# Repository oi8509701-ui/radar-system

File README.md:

X-Band T/R Module (10 GHz) with Fractal Antenna

High-performance single-channel Transmit/Receive (T/R) module for X-band phased array systems (~10–10.5 GHz), featuring integrated beamforming and a compact fractal antenna.
---------------------------------

---------------------------------

High-performance single-channel Transmit/Receive (T/R) module for X-band phased array systems (~10–10.5 GHz), featuring integrated beamforming and a compact fractal antenna.

⸻
 
 Overview

This project implements a single RF front-end module (tile) designed for scalable phased array systems.

Key features:

	•	X-band operation (~10–10.5 GHz)
	•	Integrated PA + LNA + T/R switch (QPM1002)
	•	Beamforming support (phase + amplitude control)
	•	Compact fractal antenna (14×14 mm)
	•	Designed for array scaling (e.g., 256+ elements)
	•	Optimized for automated routing (Freerouting)

⸻
 
 Architecture

RF IN → Phase Shifter → Attenuator → TXIN → [QPM1002] → ANT → Antenna
                                            ▲
RF OUT ← Phase Shifter ← Attenuator ← RXOUT ┘

QPM1002 Internal Structure:

	•	TX path: PA (~35 dBm pulsed)
	•	RX path: LNA (~2.2 dB NF, ~25 dB gain)
	•	Internal T/R switch
	•	Built-in power detector (VDET)

⸻
 
 Power Architecture

Rail	Voltage	Purpose
TX_VD	+25V	Power Amplifier
RX_VD	+10V	LNA
VDD_LOGIC	+5V	Digital logic
VDD_IO	+3.3V	Control interface
VG	-2.5V	GaN gate bias

Converters:

	•	LM5156 (SEPIC) → 25V
	•	LM5017 → 10V / 5V
	•	Charge pump → -2.5V

⸻

RF Components

Component	Function	Notes

QPM1002	T/R front-end	Core RF IC
TGP2109	Phase shifter (6-bit)	8–12 GHz
PE43705	Attenuator (6-bit)	0.5–12 GHz

⸻

 PCB
 
	•	Substrate: Rogers 4350B
	•	Stackup: 4 layers (RF + GND + PWR + CTRL)
	•	Controlled impedance (50 Ω)
	•	Dense via stitching for RF grounding
	•	Optimized for high-frequency layout

⸻

 Thermal Design

Per module dissipation:

Block	Power
PA	~8 W
DC-DC	~5.5 W
Beamforming	~1.3 W
Other	~1 W

Total: ~16 W per module

For 256 modules:

	•	Total ≈ 4 kW
	•	Requires liquid cooling

⸻
 
 Control Interface
 
	•	SPI (phase + attenuation control)
	•	GPIO (TX/RX switching)
	•	I²C (temperature sensors)

Logic:

	•	SN74HC595 (shift register)
	•	SN74LVTH573 (latch)

⸻
 
 Monitoring
 
	•	4× TMP117 temperature sensors:
	•	RF front-end
	•	Power stage
	•	Beamforming chain
	•	PCB ambient

⸻
 
 Power Sequencing

Power-Up:

	1.	Apply VG (-2.5V)
	2.	Disable TX/RX
	3.	Enable RX_VD (10V)
	4.	Enable TX_VD (25V)
	5.	Enable TX/RX

Power-Down:

	1.	Disable TX/RX
	2.	Disable TX_VD
	3.	Disable RX

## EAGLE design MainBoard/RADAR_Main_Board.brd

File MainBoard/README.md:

# Main Board — Основная плата AERIS-10

## Назначение
Основная плата обработки сигналов радара AERIS-10

## Ключевые компоненты
- **FPGA:** Xilinx Artix-7 (XC7A50T/XC7A100T)
- **MCU:** STM32F746ZGT7 (ARM Cortex-M7)
- **ADC:** AD9484 (500 MSPS, 8-bit)
- **DAC:** AD9708 (125 MSPS, 8-bit)
- **Clock:** AD9523-1
- **PLL:** 2× ADF4382ABCCZ (10.5 GHz)
- **Beamforming:** 4× ADAR1000 (16 каналов)
- **Front-end:** 16× ADTR1107
- **Mixer:** 2× LTC5552

## Функции
- Генерация LFM chirp через DAC
- Приём и оцифровка IF сигнала через ADC
- I/Q down-conversion в FPGA
- Beamforming (электронное управление лучом)
- Обработка: FFT, pulse compression, Doppler, CFAR
- USB 3.0 интерфейс (FT601)
- Управление всеми подсистемами через STM32

## Характеристики
| Параметр | Значение |
|----------|----------|
| Частота | 10.5 ГГц |
| Каналов | 16 |
| FPGA | Artix-7 50T/100T |
| ADC | 500 MSPS |
| DAC | 125 MSPS |

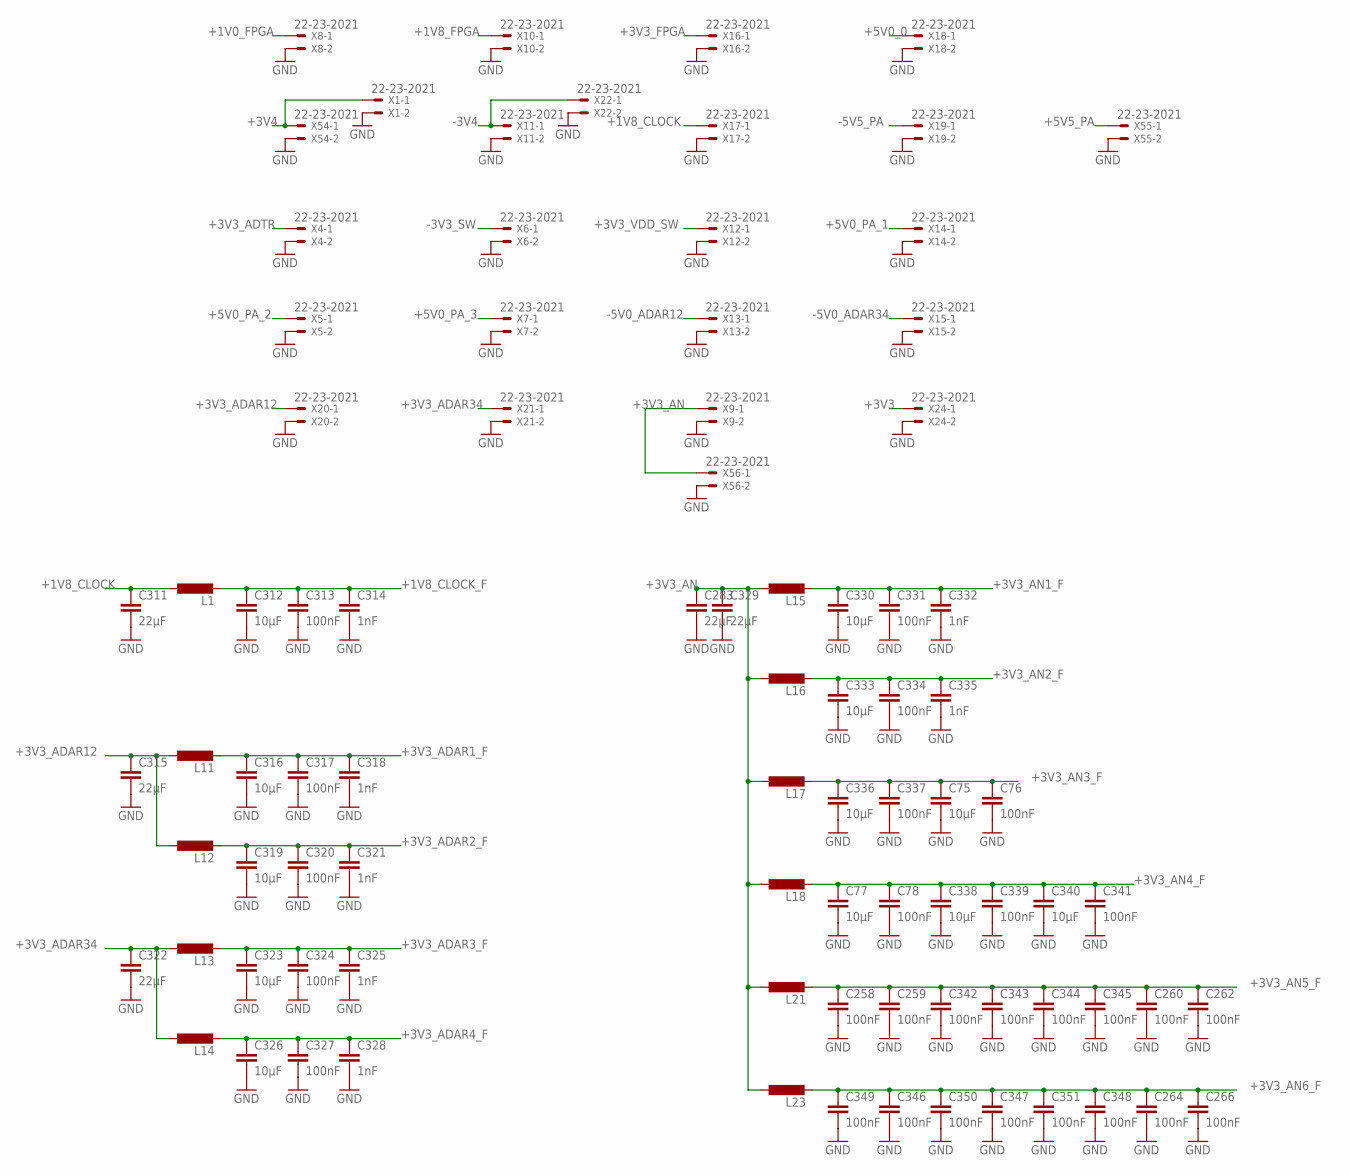
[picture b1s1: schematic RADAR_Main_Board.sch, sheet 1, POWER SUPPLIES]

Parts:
C75, C77, C312, C316, C319, C323, C326, C330, C333, C336, C338, C340: 10µF; C0805
C76, C78, C258, C259, C260, C262, C264, C266, C313, C317, C320, C324, C327, C331, C334, C337, C339, C341, C342, C343, C344, C345, C346, C347, C348, C349, C350, C351: 100nF; C0402
C283, C311, C315, C322, C329: 22µF; C1206
C314, C318, C321, C325, C328, C332, C335: 1nF; C0402
L1, L11, L12, L13, L14, L15, L16, L17, L18, L21, L23: L-EUL5650M; L5650M
X1, X4, X5, X6, X7, X8, X9, X10, X11, X12, X13, X14, X15, X16, X17, X18, X19, X20, X21, X22, X24, X54, X55, X56: 22-23-2021

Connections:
+1V0_FPGA: X8.1; also elsewhere on the board
+1V8_CLOCK: C311.1, L1.1, X17.1
+1V8_CLOCK_F: C312.1, C313.1, C314.1, L1.2; also elsewhere on the board
+1V8_FPGA: X10.1; also elsewhere on the board
+3V3: X24.1; also elsewhere on the board
+3V3_ADAR1_F: C316.1, C317.1, C318.1, L11.2; also elsewhere on the board
+3V3_ADAR2_F: C319.1, C320.1, C321.1, L12.2; also elsewhere on the board
+3V3_ADAR3_F: C323.1, C324.1, C325.1, L13.2; also elsewhere on the board
+3V3_ADAR4_F: C326.1, C327.1, C328.1, L14.2; also elsewhere on the board
+3V3_ADAR12: C315.1, L11.1, L12.1, X20.1
+3V3_ADAR34: C322.1, L13.1, L14.1, X21.1
+3V3_ADTR: X4.1; also elsewhere on the board
+3V3_AN: C283.1, C329.1, L15.1, L16.1, L17.1, L18.1, L21.1, L23.1, X9.1, X56.1; also elsewhere on the board
+3V3_AN1_F: C330.1, C331.1, C332.1, L15.2; also elsewhere on the board
+3V3_AN2_F: C333.1, C334.1, C335.1, L16.2; also elsewhere on the board
+3V3_AN3_F: C75.1, C76.1, C336.1, C337.1, L17.2; also elsewhere on the board
+3V3_AN4_F: C77.1, C78.1, C338.1, C339.1, C340.1, C341.1, L18.2; also elsewhere on the board
+3V3_AN5_F: C258.1, C259.1, C260.1, C262.1, C342.1, C343.1, C344.1, C345.1, L21.2; also elsewhere on the board
+3V3_AN6_F: C264.1, C266.1, C346.1, C347.1, C348.1, C349.1, C350.1, C351.1, L23.2; also elsewhere on the board
+3V3_FPGA: X16.1; also elsewhere on the board
+3V3_VDD_SW: X12.1; also elsewhere on the board
+3V4: X1.1, X54.1; also elsewhere on the board
+5V0_0: X18.1; also elsewhere on the board
+5V0_PA_1: X14.1; also elsewhere on the board
+5V0_PA_2: X5.1; also elsewhere on the board
+5V0_PA_3: X7.1; also elsewhere on the board
+5V5_PA: X55.1; also elsewhere on the board
-3V3_SW: X6.1; also elsewhere on the board
-3V4: X11.1, X22.1; also elsewhere on the board
-5V0_ADAR12: X13.1; also elsewhere on the board
-5V0_ADAR34: X15.1; also elsewhere on the board
-5V5_PA: X19.1; also elsewhere on the board
GND: C75.2, C76.2, C77.2, C78.2, C258.2, C259.2, C260.2, C262.2, C264.2, C266.2, C283.2, C311.2, C312.2, C313.2, C314.2, C315.2, C316.2, C317.2, C318.2, C319.2, C320.2, C321.2, C322.2, C323.2, C324.2, C325.2, C326.2, C327.2, C328.2, C329.2, C330.2, C331.2, C332.2, C333.2, C334.2, C335.2, C336.2, C337.2, C338.2, C339.2, C340.2, C341.2, C342.2, C343.2, C344.2, C345.2, C346.2, C347.2, C348.2, C349.2, C350.2, C351.2, X1.2, X4.2, X5.2, X6.2, X7.2, X8.2, X9.2, X10.2, X11.2, X12.2, X13.2, X14.2, X15.2, X16.2, X17.2, X18.2, X19.2, X20.2, X21.2, X22.2, X24.2, X54.2, X55.2, X56.2; also elsewhere on the board

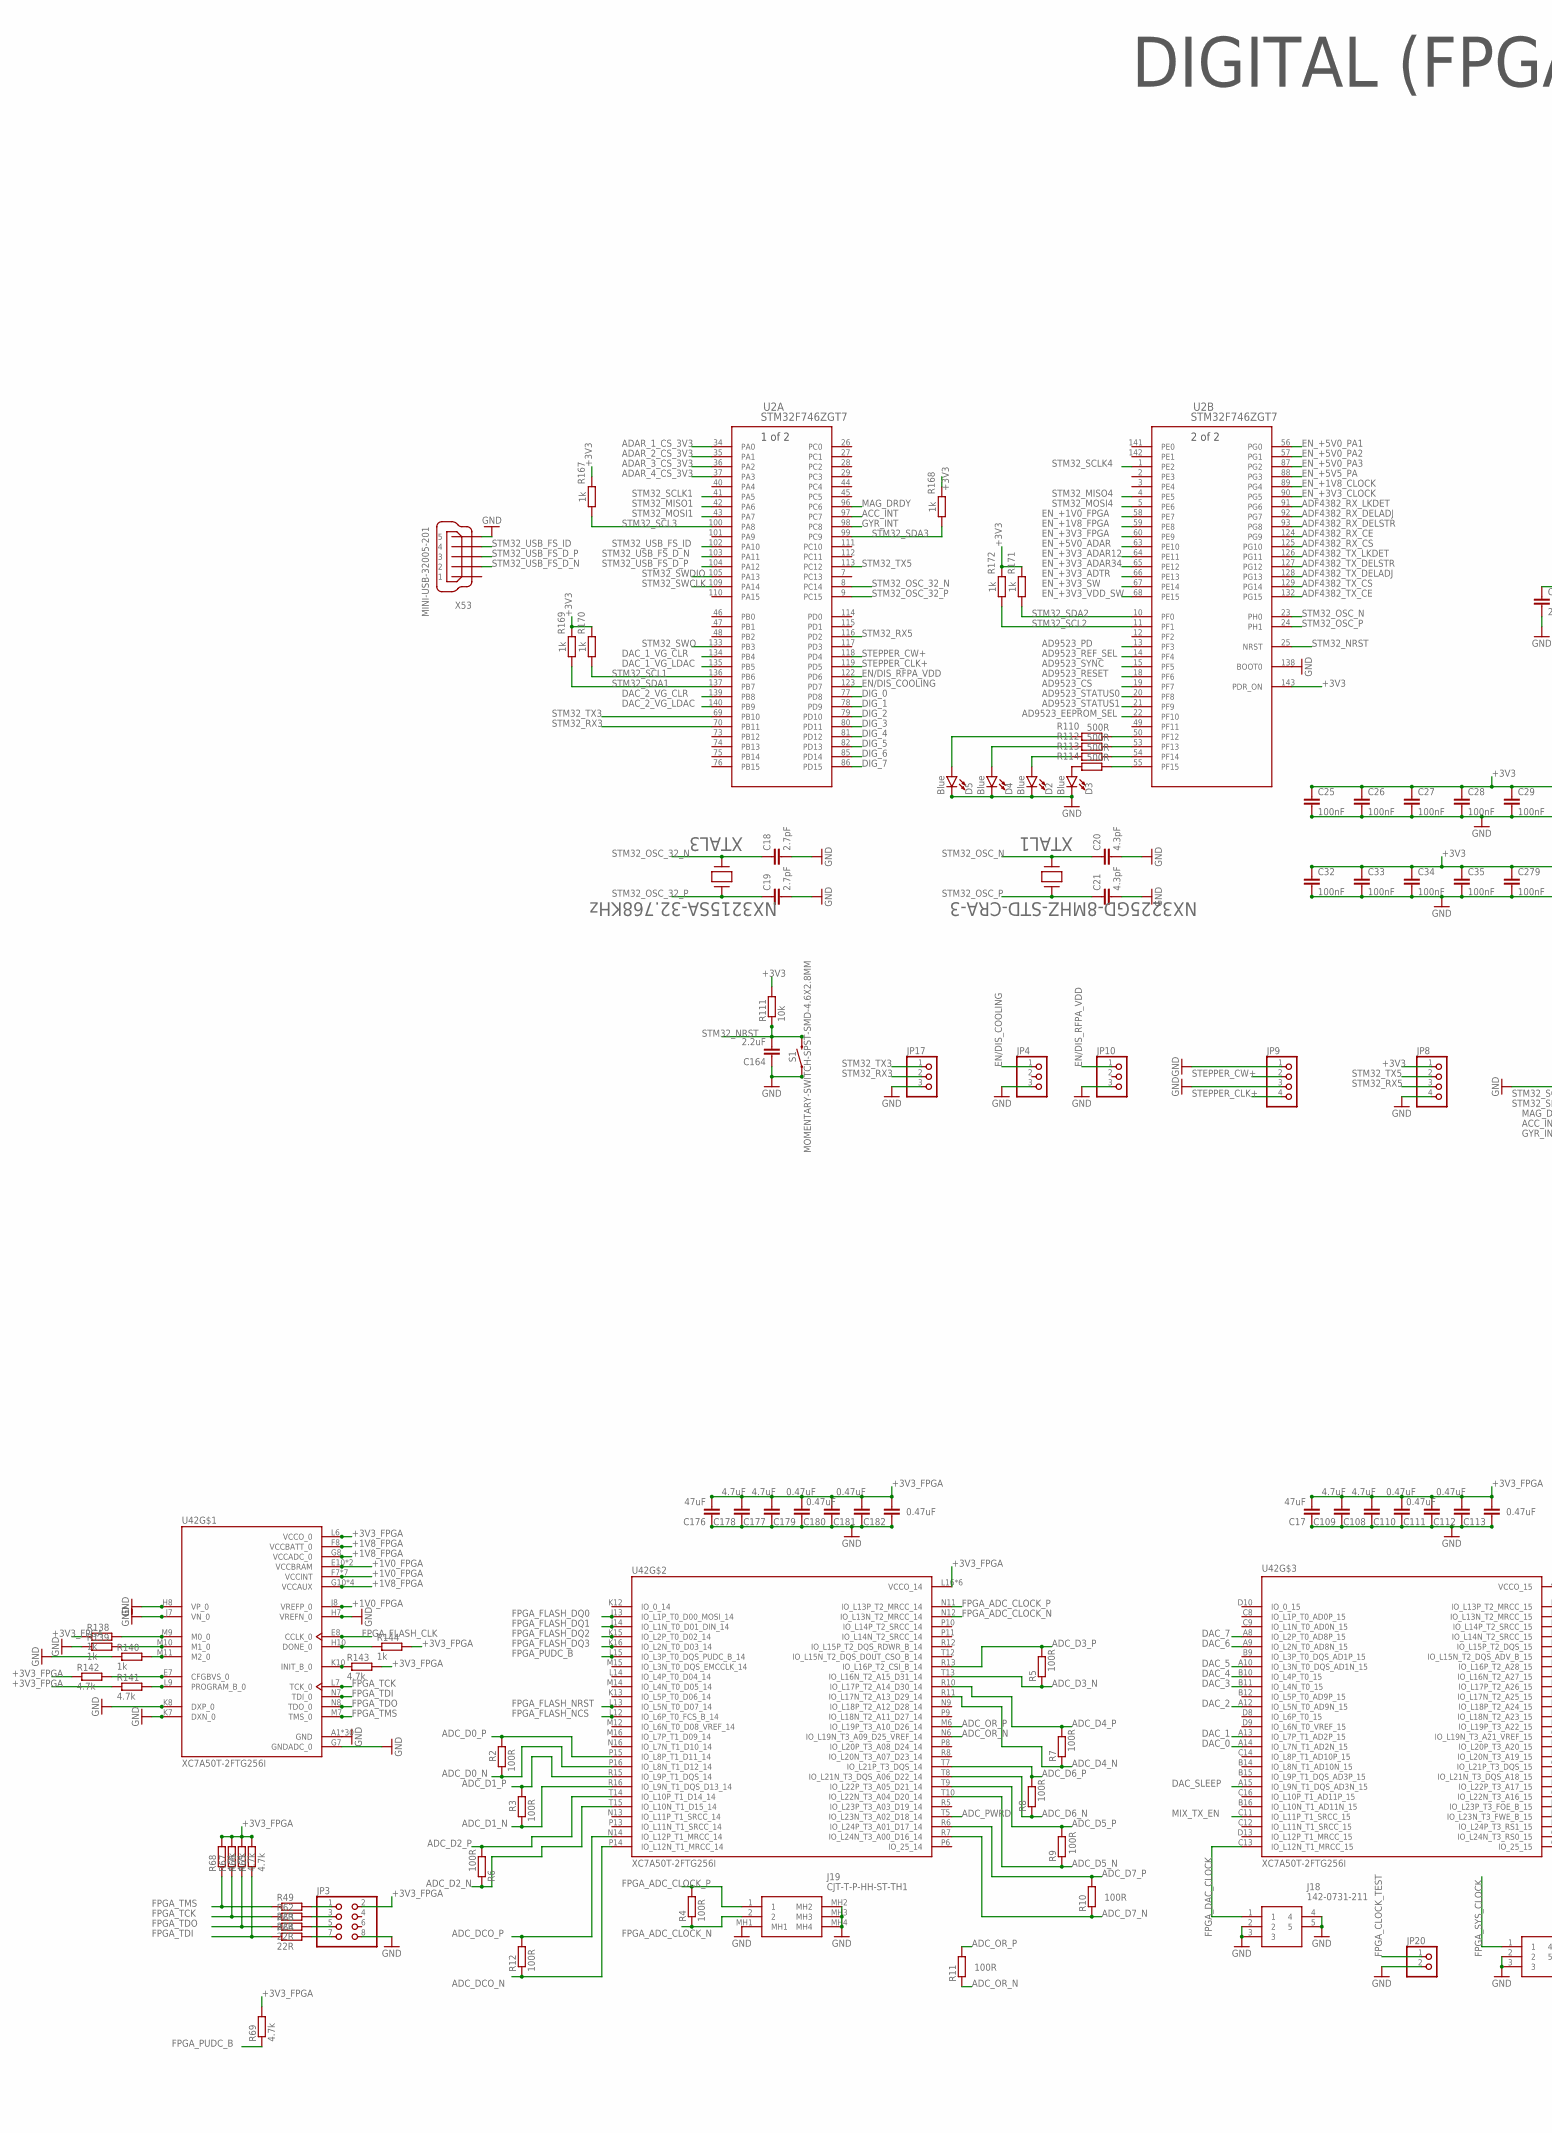
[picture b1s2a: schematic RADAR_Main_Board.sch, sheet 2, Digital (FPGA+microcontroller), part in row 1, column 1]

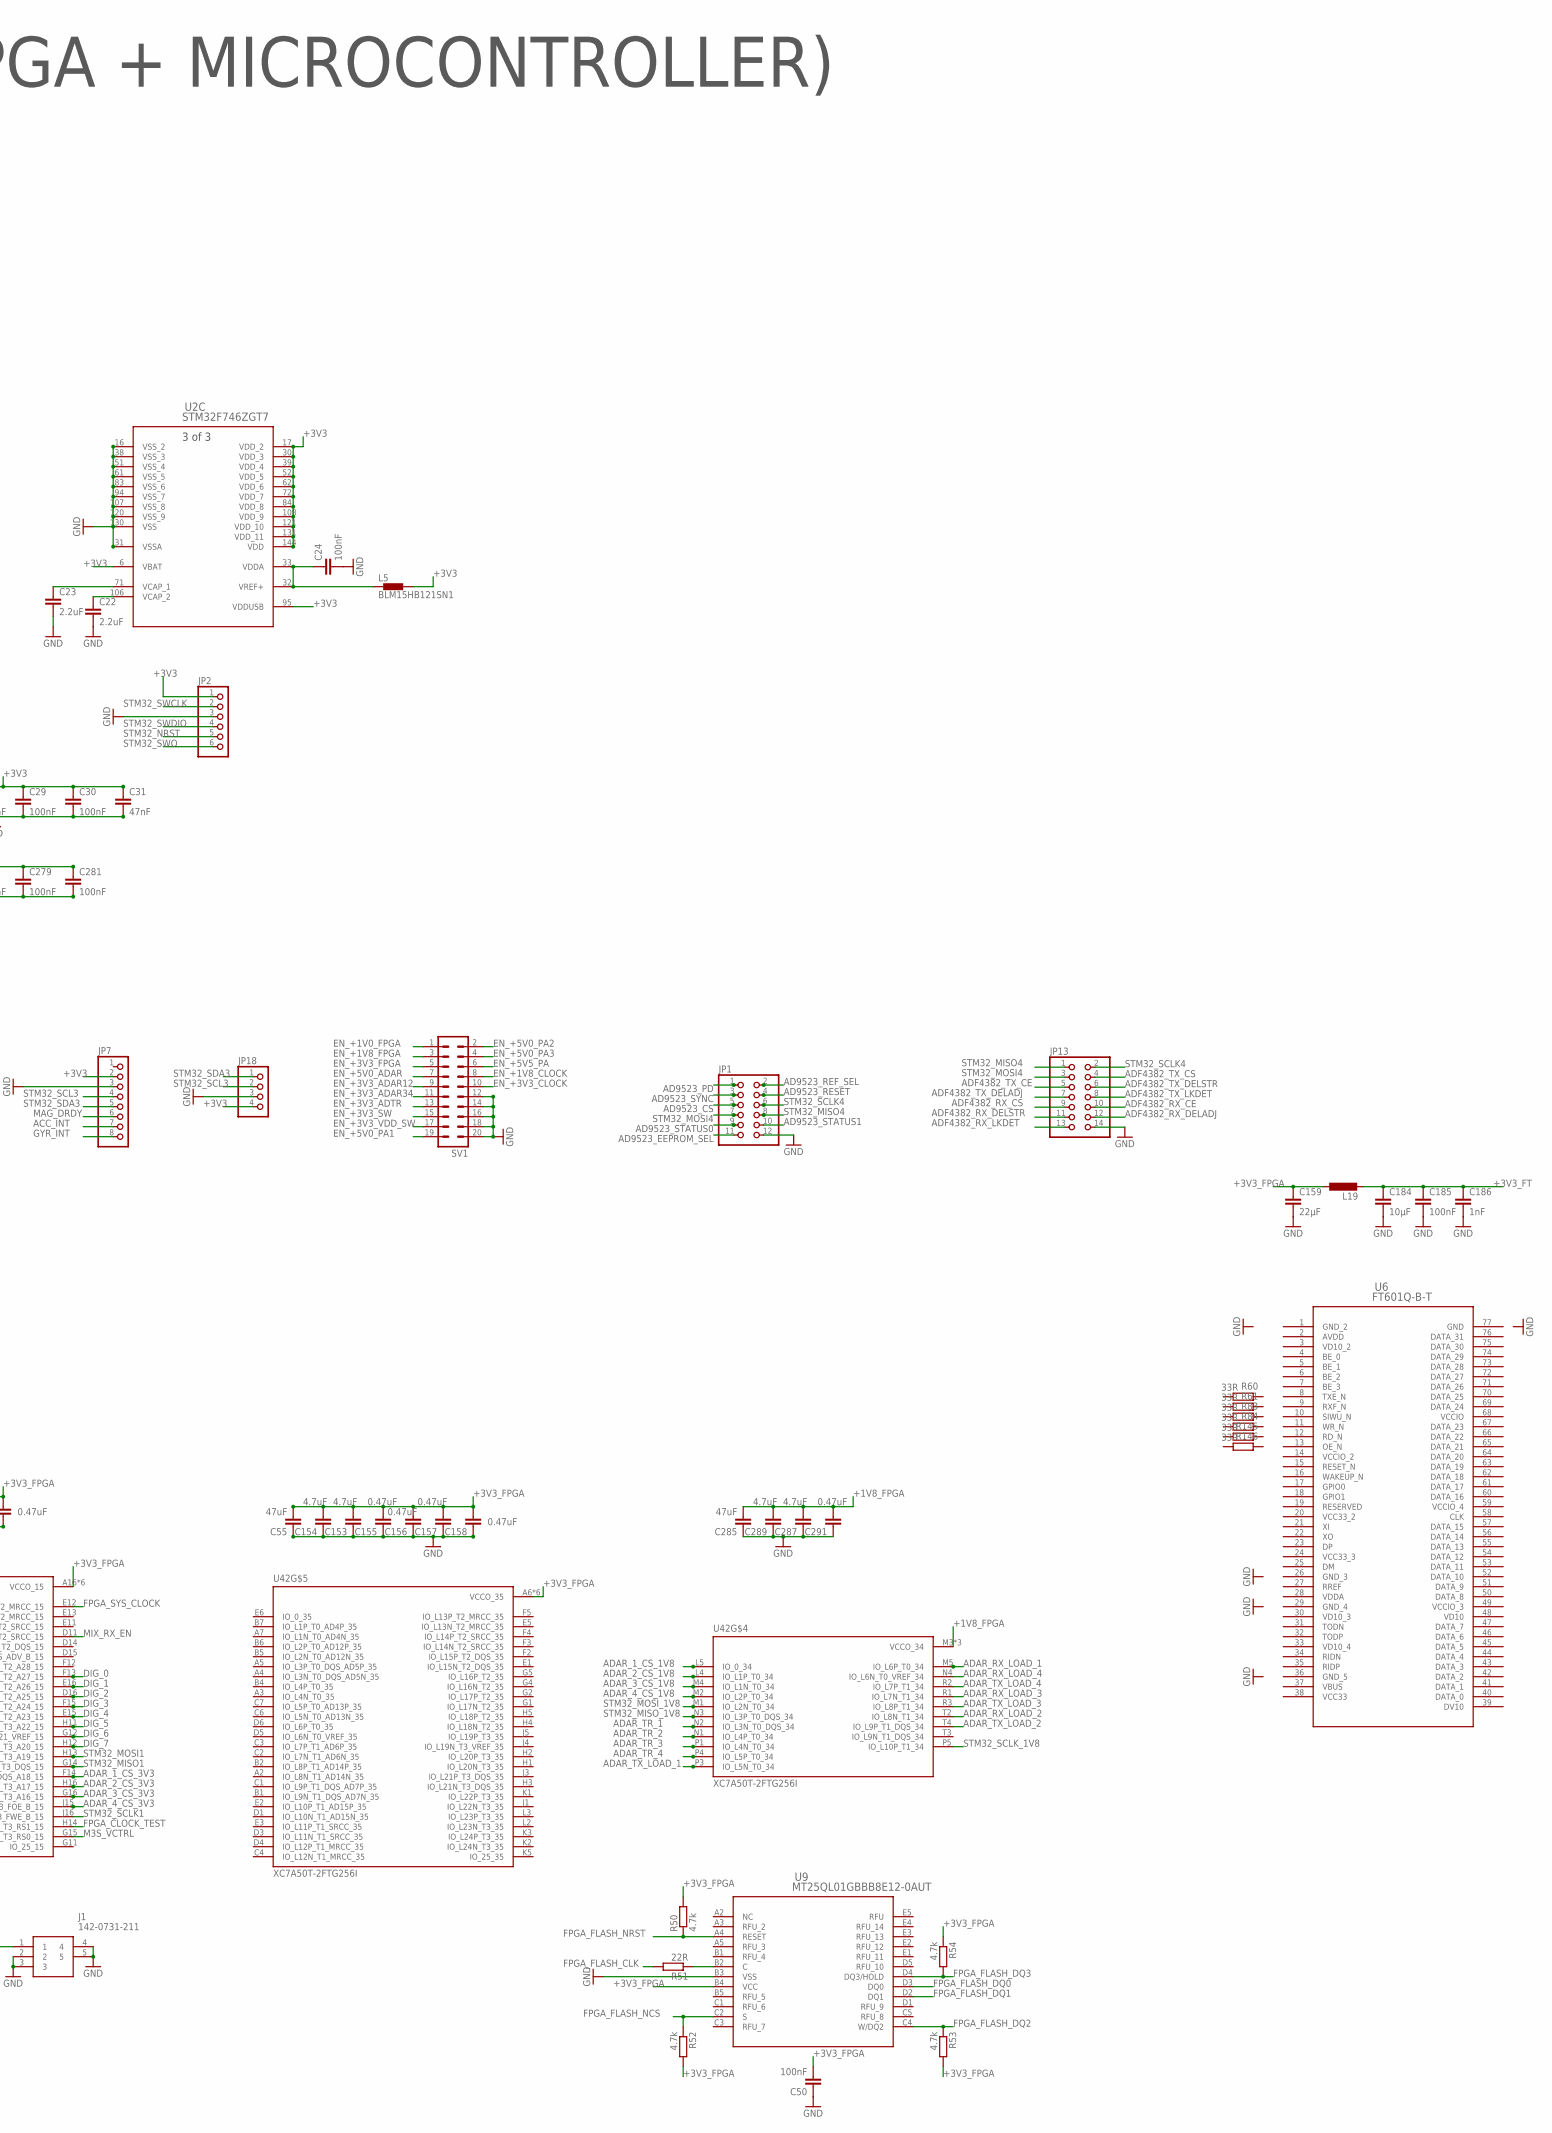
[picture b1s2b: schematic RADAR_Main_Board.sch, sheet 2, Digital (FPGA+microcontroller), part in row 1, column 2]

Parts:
C17, C55, C176, C285: 47uF; C0201
C18, C19: 2.7pF; C0201
C20, C21: 4.3pF; C0201
C22, C23, C164: 2.2uF; C0201
C24, C25, C26, C27, C28, C29, C30, C32, C33, C34, C35, C50, C279, C281: 100nF; C0201
C31: 47nF; C0201
C108, C109, C153, C154, C177, C178, C287, C289: 4.7uF; C0201
C110, C111, C112, C113, C155, C156, C157, C158, C179, C180, C181, C182, C291: 0.47uF; C0201
C159: 22µF; C1206
C184: 10µF; C0805
C185: 100nF; C0402
C186: 1nF; C0402
D2, D3, D4, D5: Blue; LED-0603
J1, J18: 142-0731-211; 1420731211
J19: CJT-T-P-HH-ST-TH1; CJTTPHHSTTH1
JP1: PINHD-2X6; 2X06
JP2: PINHD-1X6; 1X06
JP3: PINHD-2X4; 2X04
JP4, JP10, JP17: PINHD-1X3; 1X03
JP7: PINHD-1X8; 1X08
JP8, JP9, JP18: PINHD-1X4; 1X04
JP13: PINHD-2X7; 2X07
JP20: PINHD-1X2; 1X02
L5: BLM15HB121SN1; 0402
L19: L-EUL5650M; L5650M
R2, R3, R4, R5, R6, R7, R8, R9, R10, R11, R12: 100R; R0201
R49, R51, R62, R63, R64: 22R; R0201
R50, R52, R53, R54, R65, R66, R67, R68, R69, R141, R142, R143: 4.7k; R0201
R60, R61, R83, R84, R145, R146: 33R; R0201
R110, R112, R113, R114: 500R; R0201
R111: 10k; R0201
R138, R139, R140, R144, R167, R168, R169, R170, R171, R172: 1k; R0201
S1: MOMENTARY-SWITCH-SPST-SMD-4.6X2.8MM; TACTILE_SWITCH_SMD_4.6X2.8MM
SV1: MA10-2
U2: STM32F746ZGT7; LQFP-144_STM
U6: FT601Q-B-T; QFN76_FTD
U9: MT25QL01GBBB8E12-0AUT; BGA24_MT25QL_MRN
U42: XC7A50T-2FTG256I; BGA256C100P16X16_1700X1700X155
X53: MINI-USB-32005-201; 32005-201
XTAL1: NX3225GD-8MHZ-STD-CRA-3; XTAL_NX3225GD-8MHZ-STD-CRA-3_N
XTAL3: NX3215SA-32.768KHz; XTAL_NX3225GD-8MHZ-STD-CRA-3_N

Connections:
+1V0_FPGA: U42.E10 (VCCBRAM), U42.F7 (VCCINT), U42.F9 (VCCINT), U42.F11 (VCCBRAM), U42.G6 (VCCINT), U42.H9 (VCCINT), U42.J6 (VCCINT), U42.J8 (VREFP_0), U42.K9 (VCCINT), U42.L8 (VCCINT); also elsewhere on the board
+1V8_FPGA: C285.2, C287.2, C289.2, C291.2, U42.F8 (VCCBATT_0), U42.G8 (VCCADC_0), U42.G10 (VCCAUX), U42.J10 (VCCAUX), U42.K11 (VCCAUX), U42.L10 (VCCAUX), U42.M3 (VCCO_34), U42.R4 (VCCO_34), U42.T1 (VCCO_34); also elsewhere on the board
+3V3: C25.1, C26.1, C27.1, C28.1, C29.1, C30.1, C31.1, C32.1, C33.1, C34.1, C35.1, C279.1, C281.1, JP2.1, JP7.2, JP8.1, JP18.4, L5.2, R111.2, R167.1, R168.1, R169.1, R170.1, R171.1, R172.1, U2.6 (VBAT), U2.17 (VDD_2), U2.30 (VDD_3), U2.39 (VDD_4), U2.52 (VDD_5), U2.62 (VDD_6), U2.72 (VDD_7), U2.84 (VDD_8), U2.95 (VDDUSB), U2.108 (VDD_9), U2.121 (VDD_10), U2.131 (VDD_11), U2.143 (PDR_ON), U2.144 (VDD); also elsewhere on the board
+3V3_FPGA: C17.2, C50.2, C55.2, C108.2, C109.2, C110.2, C111.2, C112.2, C113.2, C153.2, C154.2, C155.2, C156.2, C157.2, C158.2, C159.1, C176.2, C177.2, C178.2, C179.2, C180.2, C181.2, C182.2, JP3.2, L19.1, R50.2, R52.2, R53.2, R54.1, R65.2, R66.2, R67.2, R68.2, R69.2, R138.1, R141.1, R142.1, R143.2, R144.2, U9.B4 (VCC), U42.A6 (VCCO_35), U42.A16 (VCCO_15), U42.B3 (VCCO_35), U42.B13 (VCCO_15), U42.C10 (VCCO_15), U42.D7 (VCCO_35), U42.E4 (VCCO_35), U42.E14 (VCCO_15), U42.F1 (VCCO_35), U42.H15 (VCCO_15), U42.J2 (VCCO_35), U42.J12 (VCCO_15), U42.L6 (VCCO_0), U42.L16 (VCCO_14), U42.M13 (VCCO_14), U42.N10 (VCCO_14), U42.P7 (VCCO_14), U42.R14 (VCCO_14), U42.T11 (VCCO_14); also elsewhere on the board
+3V3_FT: C184.1, C185.1, C186.1, L19.2
ACC_INT: JP7.7, U2.97 (PC7)
AD9523_CS: JP1.5, U2.19 (PF7)
AD9523_EEPROM_SEL: JP1.11, U2.22 (PF10)
AD9523_PD: JP1.1, U2.13 (PF3)
AD9523_REF_SEL: JP1.2, U2.14 (PF4)
AD9523_RESET: JP1.4, U2.18 (PF6)
AD9523_STATUS0: JP1.9, U2.20 (PF8)
AD9523_STATUS1: JP1.10, U2.21 (PF9)
AD9523_SYNC: JP1.3, U2.15 (PF5)
ADAR_1_CS_1V8: U42.L5 (IO_0_34); also elsewhere on the board
ADAR_1_CS_3V3: U2.34 (PA0), U42.F14 (IO_L21N_T3_DQS_A18_15)
ADAR_2_CS_1V8: U42.L4 (IO_L1P_T0_34); also elsewhere on the board
ADAR_2_CS_3V3: U2.35 (PA1), U42.H16 (IO_L22P_T3_A17_15)
ADAR_3_CS_1V8: U42.M4 (IO_L1N_T0_34); also elsewhere on the board
ADAR_3_CS_3V3: U2.36 (PA2), U42.G16 (IO_L22N_T3_A16_15)
ADAR_4_CS_1V8: U42.M2 (IO_L2P_T0_34); also elsewhere on the board
ADAR_4_CS_3V3: U2.37 (PA3), U42.J15 (IO_L23P_T3_FOE_B_15)
ADAR_RX_LOAD_1: U42.M5 (IO_L6P_T0_34); also elsewhere on the board
ADAR_RX_LOAD_2: U42.T2 (IO_L8N_T1_34); also elsewhere on the board
ADAR_RX_LOAD_3: U42.R1 (IO_L7N_T1_34); also elsewhere on the board
ADAR_RX_LOAD_4: U42.N4 (IO_L6N_T0_VREF_34); also elsewhere on the board
ADAR_TR_1: U42.N2 (IO_L3N_T0_DQS_34); also elsewhere on the board
ADAR_TR_2: U42.N1 (IO_L4P_T0_34); also elsewhere on the board
ADAR_TR_3: U42.P1 (IO_L4N_T0_34); also elsewhere on the board
ADAR_TR_4: U42.P4 (IO_L5P_T0_34); also elsewhere on the board
ADAR_TX_LOAD_1: U42.P3 (IO_L5N_T0_34); also elsewhere on the board
ADAR_TX_LOAD_2: U42.T4 (IO_L9P_T1_DQS_34); also elsewhere on the board
ADAR_TX_LOAD_3: U42.R3 (IO_L8P_T1_34); also elsewhere on the board
ADAR_TX_LOAD_4: U42.R2 (IO_L7P_T1_34); also elsewhere on the board
ADC_D0_N: R2.1, U42.P16 (IO_L8N_T1_D12_14); also elsewhere on the board
ADC_D0_P: R2.2, U42.P15 (IO_L8P_T1_D11_14); also elsewhere on the board
ADC_D1_N: R3.1, U42.R16 (IO_L9N_T1_DQS_D13_14); also elsewhere on the board
ADC_D1_P: R3.2, U42.R15 (IO_L9P_T1_DQS_14); also elsewhere on the board
ADC_D2_N: R6.1, U42.T15 (IO_L10N_T1_D15_14); also elsewhere on the board
ADC_D2_P: R6.2, U42.T14 (IO_L10P_T1_D14_14); also elsewhere on the board
ADC_D3_N: R5.1, U42.T13 (IO_L16N_T2_A15_D31_14); also elsewhere on the board
ADC_D3_P: R5.2, U42.R13 (IO_L16P_T2_CSI_B_14); also elsewhere on the board
ADC_D4_N: R7.1, U42.R11 (IO_L17N_T2_A13_D29_14); also elsewhere on the board
ADC_D4_P: R7.2, U42.R10 (IO_L17P_T2_A14_D30_14); also elsewhere on the board
ADC_D5_N: R9.1, U42.T10 (IO_L22N_T3_A04_D20_14); also elsewhere on the board
ADC_D5_P: R9.2, U42.T9 (IO_L22P_T3_A05_D21_14); also elsewhere on the board
ADC_D6_N: R8.1, U42.T8 (IO_L21N_T3_DQS_A06_D22_14); also elsewhere on the board
ADC_D6_P: R8.2, U42.T7 (IO_L21P_T3_DQS_14); also elsewhere on the board
ADC_D7_N: R10.1, U42.R7 (IO_L24N_T3_A00_D16_14); also elsewhere on the board
ADC_D7_P: R10.2, U42.R6 (IO_L24P_T3_A01_D17_14); also elsewhere on the board
ADC_DCO_N: R12.1, U42.P14 (IO_L12N_T1_MRCC_14); also elsewhere on the board
ADC_DCO_P: R12.2, U42.N14 (IO_L12P_T1_MRCC_14); also elsewhere on the board
ADC_OR_N: R11.1, U42.N6 (IO_L19N_T3_A09_D25_VREF_14); also elsewhere on the board
ADC_OR_P: R11.2, U42.M6 (IO_L19P_T3_A10_D26_14); also elsewhere on the board
ADC_PWRD: U42.T5 (IO_L23N_T3_A02_D18_14); also elsewhere on the board
ADF4382_RX_CE: JP13.10, U2.124 (PG9)
ADF4382_RX_CS: JP13.9, U2.125 (PG10)
ADF4382_RX_DELADJ: JP13.12, U2.92 (PG7)
ADF4382_RX_DELSTR: JP13.11, U2.93 (PG8)
ADF4382_RX_LKDET: JP13.13, U2.91 (PG6)
ADF4382_TX_CE: JP13.5, U2.132 (PG15)
ADF4382_TX_CS: JP13.4, U2.129 (PG14)
ADF4382_TX_DELADJ: JP13.7, U2.128 (PG13)
ADF4382_TX_DELSTR: JP13.6, U2.127 (PG12)
ADF4382_TX_LKDET: JP13.8, U2.126 (PG11)
AVDD: U6.2 (AVDD)
DAC_0: U42.A14 (IO_L7N_T1_AD2N_15); also elsewhere on the board
DAC_1: U42.A13 (IO_L7P_T1_AD2P_15); also elsewhere on the board
DAC_1_VG_CLR: U2.134 (PB4); also elsewhere on the board
DAC_1_VG_LDAC: U2.135 (PB5); also elsewhere on the board
DAC_2: U42.A12 (IO_L5N_T0_AD9N_15); also elsewhere on the board
DAC_2_VG_CLR: U2.139 (PB8); also elsewhere on the board
DAC_2_VG_LDAC: U2.140 (PB9); also elsewhere on the board
DAC_3: U42.B11 (IO_L4N_T0_15); also elsewhere on the board
DAC_4: U42.B10 (IO_L4P_T0_15); also elsewhere on the board
DAC_5: U42.A10 (IO_L3N_T0_DQS_AD1N_15); also elsewhere on the board
DAC_6: U42.A9 (IO_L2N_T0_AD8N_15); also elsewhere on the board
DAC_7: U42.A8 (IO_L2P_T0_AD8P_15); also elsewhere on the board
DAC_SLEEP: U42.A15 (IO_L9N_T1_DQS_AD3N_15); also elsewhere on the board
DIG_0: U2.77 (PD8), U42.F13 (IO_L16N_T2_A27_15)
DIG_1: U2.78 (PD9), U42.E16 (IO_L17P_T2_A26_15)
DIG_2: U2.79 (PD10), U42.D16 (IO_L17N_T2_A25_15)
DIG_3: U2.80 (PD11), U42.F15 (IO_L18P_T2_A24_15)
DIG_4: U2.81 (PD12), U42.E15 (IO_L18N_T2_A23_15)
DIG_5: U2.82 (PD13), U42.H11 (IO_L19P_T3_A22_15)
DIG_6: U2.85 (PD14), U42.G12 (IO_L19N_T3_A21_VREF_15)
DIG_7: U2.86 (PD15), U42.H12 (IO_L20P_T3_A20_15)
EN/DIS_COOLING: JP4.1, U2.123 (PD7)
EN/DIS_RFPA_VDD: JP10.1, U2.122 (PD6)
EN_+1V0_FPGA: SV1.1, U2.58 (PE7)
EN_+1V8_CLOCK: SV1.8, U2.89 (PG4)
EN_+1V8_FPGA: SV1.3, U2.59 (PE8)
EN_+3V3_ADAR12: SV1.9, U2.64 (PE11)
EN_+3V3_ADAR34: SV1.11, U2.65 (PE12)
EN_+3V3_ADTR: SV1.13, U2.66 (PE13)
EN_+3V3_CLOCK: SV1.10, U2.90 (PG5)
EN_+3V3_FPGA: SV1.5, U2.60 (PE9)
EN_+3V3_SW: SV1.15, U2.67 (PE14)
EN_+3V3_VDD_SW: SV1.17, U2.68 (PE15)
EN_+5V0_ADAR: SV1.7, U2.63 (PE10)
EN_+5V0_PA1: SV1.19, U2.56 (PG0)
EN_+5V0_PA2: SV1.2, U2.57 (PG1)
EN_+5V0_PA3: SV1.4, U2.87 (PG2)
EN_+5V5_PA: SV1.6, U2.88 (PG3)
FPGA_ADC_CLOCK_N: J19.2, R4.1, U42.N12 (IO_L13N_T2_MRCC_14)
FPGA_ADC_CLOCK_P: J19.1, R4.2, U42.N11 (IO_L13P_T2_MRCC_14)
FPGA_CLOCK_TEST: JP20.1, U42.H14 (IO_L24P_T3_RS1_15)
FPGA_DAC_CLOCK: J18.1, U42.C13 (IO_L12N_T1_MRCC_15)
FPGA_FLASH_CLK: R51.2, U42.E8 (CCLK_0)
FPGA_FLASH_DQ0: U9.D3 (DQ0), U42.J13 (IO_L1P_T0_D00_MOSI_14)
FPGA_FLASH_DQ1: U9.D2 (DQ1), U42.J14 (IO_L1N_T0_D01_DIN_14)
FPGA_FLASH_DQ2: R53.1, U9.C4 (W/DQ2), U42.K15 (IO_L2P_T0_D02_14)
FPGA_FLASH_DQ3: R54.2, U9.D4 (DQ3/HOLD), U42.K16 (IO_L2N_T0_D03_14)
FPGA_FLASH_NCS: R52.1, U9.C2 (S), U42.L12 (IO_L6P_T0_FCS_B_14)
FPGA_FLASH_NRST: R50.1, U9.A4 (RESET), U42.L13 (IO_L5N_T0_D07_14)
FPGA_PUDC_B: R69.1, U42.L15 (IO_L3P_T0_DQS_PUDC_B_14)
FPGA_SYS_CLOCK: J1.1, U42.E12 (IO_L13P_T2_MRCC_15)
FPGA_TCK: R62.1, R67.1, U42.L7 (TCK_0)
FPGA_TDI: R64.1, R65.1, U42.N7 (TDI_0)
FPGA_TDO: R63.1, R66.1, U42.N8 (TDO_0)
FPGA_TMS: R49.1, R68.1, U42.M7 (TMS_0)
GND: C17.1, C18.2, C19.2, C20.2, C21.2, C22.2, C23.2, C24.2, C25.2, C26.2, C27.2, C28.2, C29.2, C30.2, C31.2, C32.2, C33.2, C34.2, C35.2, C50.1, C55.1, C108.1, C109.1, C110.1, C111.1, C112.1, C113.1, C153.1, C154.1, C155.1, C156.1, C157.1, C158.1, C159.2, C164.1, C176.1, C177.1, C178.1, C179.1, C180.1, C181.1, C182.1, C184.2, C185.2, C186.2, C279.2, C281.2, C285.1, C287.1, C289.1, C291.1, D2.C, D3.C, D4.C, D5.C, J1.2, J1.3, J1.4, J1.5, J18.2, J18.3, J18.4, J18.5, J19.MH1, J19.MH2, J19.MH3, J19.MH4, JP1.12, JP2.3, JP3.8, JP4.3, JP7.3, JP8.4, JP9.1, JP9.3, JP10.3, JP13.14, JP17.3, JP18.3, JP20.2, R139.1, R140.1, S1.1, S1.2 (1), SV1.12, SV1.14, SV1.16, SV1.18, SV1.20, U2.16 (VSS_2), U2.31 (VSSA), U2.38 (VSS_3), U2.51 (VSS_4), U2.61 (VSS_5), U2.83 (VSS_6), U2.94 (VSS_7), U2.107 (VSS_8), U2.120 (VSS_9), U2.130 (VSS), U2.138 (BOOT0), U9.B3 (VSS), U42.A1 (GND), U42.A11 (GND), U42.B8 (GND), U42.C5 (GND), U42.C15 (GND), U42.D2 (GND), U42.D12 (GND), U42.E9 (GND), U42.F6 (GND), U42.F10 (GND), U42.F16 (GND), U42.G3 (GND), U42.G7 (GNDADC_0), U42.G9 (GND), U42.G13 (GND), U42.H6 (GND), U42.H7 (VREFN_0), U42.H8 (VP_0), U42.J7 (VN_0), U42.J9 (GND), U42.J11 (GND), U42.K4 (GND), U42.K6 (GND), U42.K7 (DXN_0), U42.K8 (DXP_0), U42.K14 (GND), U42.L1 (GND), U42.L11 (GND), U42.M8 (GND), U42.N5 (GND), U42.N15 (GND), U42.P2 (GND), U42.P12 (GND), U42.R9 (GND), U42.T6 (GND), U42.T16 (GND), X53.5; also elsewhere on the board
GYR_INT: JP7.8, U2.98 (PC8)
M3S_VCTRL: U42.G15 (IO_L24N_T3_RS0_15); also elsewhere on the board
MAG_DRDY: JP7.6, U2.96 (PC6)
MIX_RX_EN: U42.D11 (IO_L14N_T2_SRCC_15); also elsewhere on the board
MIX_TX_EN: U42.C11 (IO_L11P_T1_SRCC_15); also elsewhere on the board
unnamed: C23.1, U2.71 (VCAP_1)
unnamed: C22.1, U2.106 (VCAP_2)
unnamed: C24.1, L5.1, U2.32 (VREF+), U2.33 (VDDA)
unnamed: R51.1, U9.B2 (C)
unnamed: JP3.1, R49.2
unnamed: JP3.3, R62.2
unnamed: JP3.5, R63.2
unnamed: JP3.7, R64.2
unnamed: R110.2, U2.50 (PF12)
unnamed: R112.2, U2.53 (PF13)
unnamed: D3.A, R114.1
unnamed: R113.2, U2.54 (PF14)
unnamed: R114.2, U2.55 (PF15)
unnamed: D2.A, R113.1
unnamed: D4.A, R112.1
unnamed: D5.A, R110.1
unnamed: R138.2, U42.M9 (M0_0)
unnamed: R139.2, U42.M10 (M1_0)
unnamed: R140.2, U42.M11 (M2_0)
unnamed: R141.2, U42.L9 (PROGRAM_B_0)
unnamed: R142.2, U42.E7 (CFGBVS_0)
unnamed: R144.1, U42.H10 (DONE_0)
unnamed: R143.1, U42.K10 (INIT_B_0)
STEPPER_CLK+: JP9.4, U2.119 (PD5)
STEPPER_CW+: JP9.2, U2.118 (PD4)
STM32_MISO1: U2.42 (PA6), U42.G14 (IO_L21P_T3_DQS_15)
STM32_MISO4: JP1.8, JP13.1, U2.4 (PE5)
STM32_MISO_1V8: U42.N3 (IO_L3P_T0_DQS_34); also elsewhere on the board
STM32_MOSI1: U2.43 (PA7), U42.H13 (IO_L20N_T3_A19_15)
STM32_MOSI4: JP1.7, JP13.3, U2.5 (PE6)
STM32_MOSI_1V8: U42.M1 (IO_L2N_T0_34); also elsewhere on the board
STM32_NRST: C164.2, JP2.5, R111.1, S1.3 (2), S1.4 (2), U2.25 (NRST)
STM32_OSC_32_N: C18.1, U2.8 (PC14), XTAL3.2
STM32_OSC_32_P: C19.1, U2.9 (PC15), XTAL3.1
STM32_OSC_N: C20.1, U2.23 (PH0), XTAL1.2
STM32_OSC_P: C21.1, U2.24 (PH1), XTAL1.1
STM32_RX3: JP17.2, U2.70 (PB11)
STM32_RX5: JP8.3, U2.116 (PD2)
STM32_SCL1: R170.2, U2.136 (PB6); also elsewhere on the board
STM32_SCL2: R172.2, U2.11 (PF1); also elsewhere on the board
STM32_SCL3: JP7.4, JP18.2, R167.2, U2.100 (PA8)
STM32_SCLK1: U2.41 (PA5), U42.J16 (IO_L23N_T3_FWE_B_15)
STM32_SCLK4: JP1.6, JP13.2, U2.1 (PE2)
STM32_SCLK_1V8: U42.P5 (IO_L10P_T1_34); also elsewhere on the board
STM32_SDA1: R169.2, U2.137 (PB7); also elsewhere on the board
STM32_SDA2: R171.2, U2.10 (PF0); also elsewhere on the board
STM32_SDA3: JP7.5, JP18.1, R168.2, U2.99 (PC9)
STM32_SWCLK: JP2.2, U2.109 (PA14)
STM32_SWDIO: JP2.4, U2.105 (PA13)
STM32_SWO: JP2.6, U2.133 (PB3)
STM32_TX3: JP17.1, U2.69 (PB10)
STM32_TX5: JP8.2, U2.113 (PC12)
STM32_USB_FS_D_N: U2.103 (PA11), X53.2
STM32_USB_FS_D_P: U2.104 (PA12), X53.3
STM32_USB_FS_ID: U2.102 (PA10), X53.4
VBUS: U6.37 (VBUS)
VCC33: U6.38 (VCC33)
VCC33_2: U6.20 (VCC33_2)
VCC33_3: U6.24 (VCC33_3)
VCCIO: U6.68 (VCCIO)
VCCIO_2: U6.14 (VCCIO_2)
VCCIO_3: U6.49 (VCCIO_3)
VCCIO_4: U6.59 (VCCIO_4)
VDDA: U6.28 (VDDA)

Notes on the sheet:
DIGITAL (FPGA + MICROCONTROLLER)

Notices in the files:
parts and their libraries:
SparkFun-LED: Licensing: Creative Commons ShareAlike 4.0 International - https://creativecommons.org/licenses/by-sa/4.0
COPYRIGHT: Copyright (C) 2024 Ultra Librarian. All rights reserved.
COPYRIGHT: Copyright (C) 2025 Ultra Librarian. All rights reserved.
